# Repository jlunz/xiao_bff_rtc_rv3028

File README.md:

## XIAO / BFF - RTC RV3028 Add-On 

### Description

Add-On board for XIAO or QT Py boards.  
Uses an [RV3028](https://www.microcrystal.com/en/products/real-time-clock-rtc-modules/rv-3028-c7) and provides footprints for MLCC or supercapacitor V<sub>BACKUP</sub> source.

Datasheet: https://www.microcrystal.com/fileadmin/Media/Products/RTC/Datasheet/RV-3028-C7.pdf  
Application Manual: https://www.microcrystal.com/fileadmin/Media/Products/RTC/App.Manual/RV-3028-C7_App-Manual.pdf

Based on:  
https://github.com/Seeed-Studio/OPL_Kicad_Library/tree/master/Seeed%20Studio%20XIAO%20Series%20Library

Alternatives:
- https://shop.pimoroni.com/products/rv3028-real-time-clock-rtc-breakout?variant=27926940549203
- https://www.mikroe.com/rtc-8-click
- https://core-electronics.com.au/piicodev-real-time-clock-rv3028.html
- https://www.melopero.com/en/shop/melopero/meloperorv3028realtimeclockbreakoutqwiic/

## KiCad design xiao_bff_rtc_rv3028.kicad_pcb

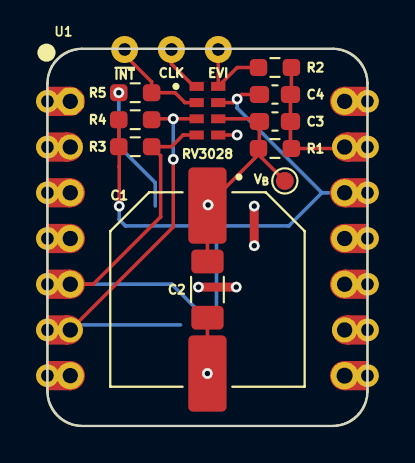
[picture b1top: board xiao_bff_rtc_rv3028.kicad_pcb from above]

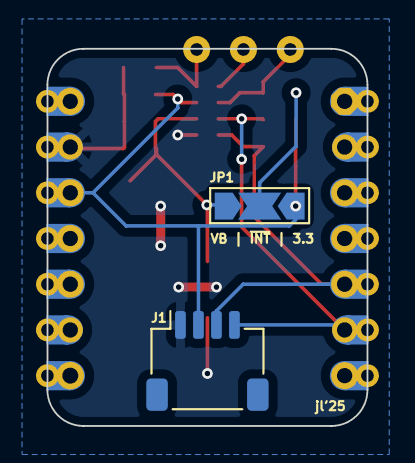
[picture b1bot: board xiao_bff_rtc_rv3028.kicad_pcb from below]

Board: 2 copper layers, 17.8 x 21.0 mm, 16 parts (2 on the bottom side), 9 nets.

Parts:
C1: FC0H104ZFTBR24; CAPAE1080X580N
C2: 100µ; C_1206_3216Metric_Pad1.33x1.80mm_HandSolder
C3, C4: 100n; C_0603_1608Metric_Pad1.08x0.95mm_HandSolder
CLK: TestPoint CLKOUT; TestPoint_THTPad_D1.5mm_Drill0.7mm
EVI: TestPoint EVI; TestPoint_THTPad_D1.5mm_Drill0.7mm
J1: Conn_01x04_Pin; JST_SH_SM04B-SRSS-TB_1x04-1MP_P1.00mm_Horizontal
JP1: SolderJumper_3_Open; SolderJumper-3_P2.0mm_Open_TrianglePad1.0x1.5mm_NumberLabels
R1, R2, R3, R4, R5: 10k; R_0603_1608Metric_Pad0.98x0.95mm_HandSolder
RV3028: RV-3028-C7_32.768KHZ_1PPM-TA-QC; IC_RV-3028-C7_32.768KHZ_1PPM-TA-QC
U1: XIAO-ADDON; XIAO-Add-On
V_{B}: TestPoint VBackup; TestPoint_Pad_D1.0mm

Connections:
+3.3V: C4.1, J1.2, JP1.3 (B), R3.2, R4.2, RV3028.7 (VDD), U1.12 (3V3)
CLKOUT: CLK.1, RV3028.1 (CLKOUT)
EVI: EVI.1, R2.2, RV3028.8 (EVI)
GND: C1.2, C2.2, C3.2, C4.2, J1.1, R1.2, R2.1, RV3028.5 (VSS), U1.13 (GND)
unnamed: JP1.2 (C), R5.2
SCL: J1.4, R4.1, RV3028.3 (SCL), U1.6 (GPIO23/D5/SCL)
SDA: J1.3, R3.1, RV3028.4 (SDA), U1.5 (GPIO22/D4/SDA)
VBackup: C1.1, C2.1, C3.1, JP1.1 (A), R1.1, RV3028.6 (VBACKUP), V_{B}.1
~INT: R5.1, RV3028.2 (~INT)

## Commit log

2025-06-07 Start RV3028 Add-On
2025-06-07 Create LICENSE
